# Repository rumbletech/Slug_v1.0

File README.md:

# Slug_v1.0
Slug ( Slog/Serial Logger ) is an open source firmware and an open source hardware project , it implements logging of serial buses like USART,I2C,SPI to an SD Card.

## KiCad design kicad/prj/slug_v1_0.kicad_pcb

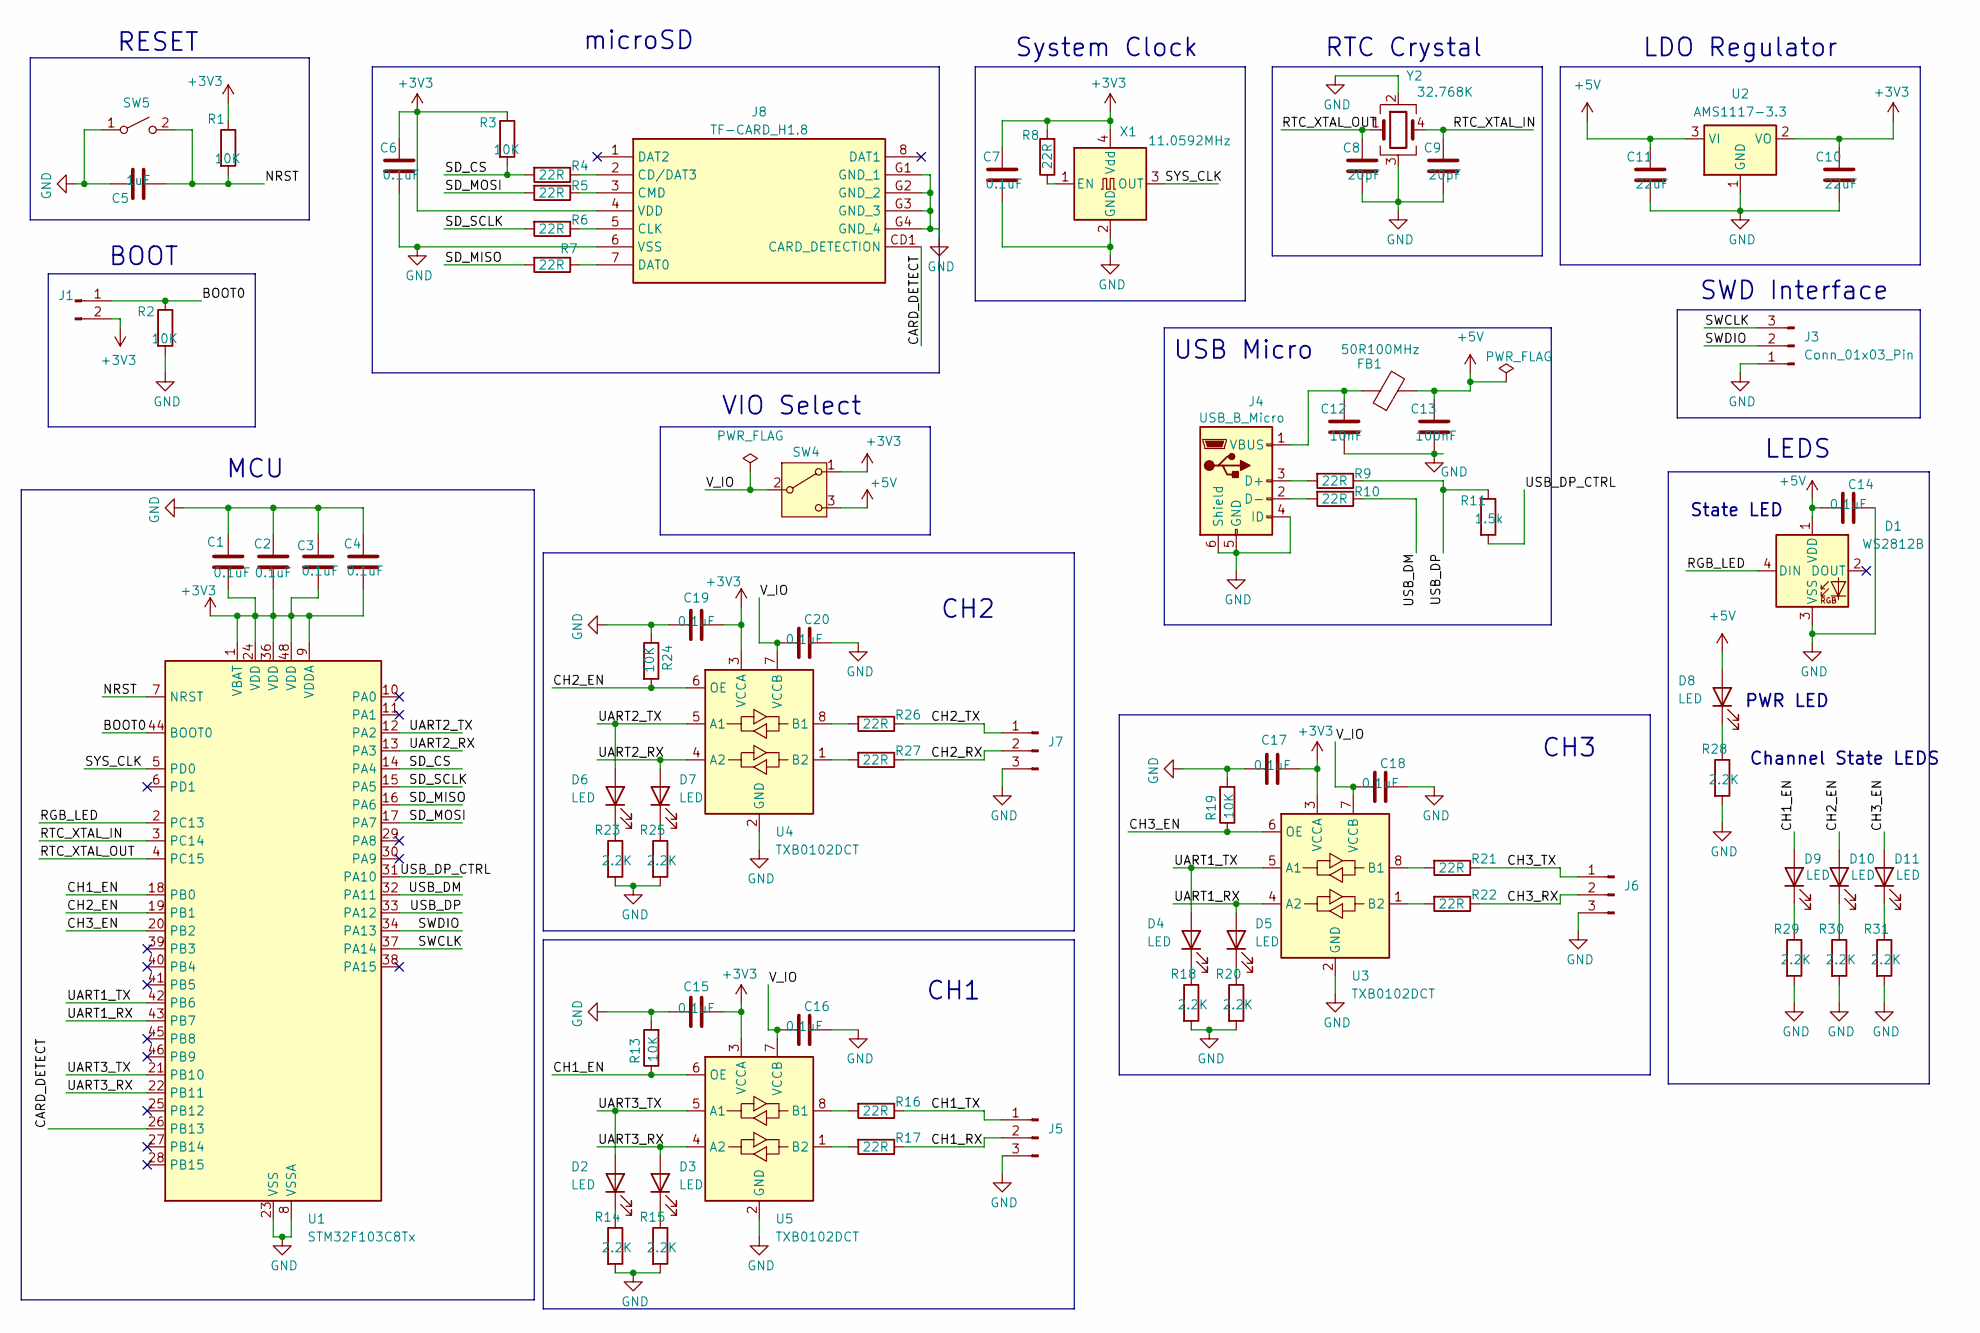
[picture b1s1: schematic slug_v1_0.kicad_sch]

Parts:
C1, C2, C3, C4, C6, C7, C14, C15, C16, C17, C18, C19, C20: 0.1uF; C_0805_2012Metric
C5: 1uF; C_0805_2012Metric
C8, C9: 20pF; C_0805_2012Metric
C10, C11: 22uF; C_0805_2012Metric
C12: 10nF; C_0805_2012Metric
C13: 100nF; C_0805_2012Metric
D1: WS2812B; LED_WS2812B_PLCC4_5.0x5.0mm_P3.2mm
D2, D3, D4, D5, D6, D7, D8, D9, D10, D11: LED; LED_0805_2012Metric
FB1: 50R100MHz; L_0805_2012Metric
J1: Conn_01x02_Pin; PinHeader_1x02_P2.54mm_Vertical
J3: Conn_01x03_Pin; PinHeader_1x03_P2.54mm_Vertical
J4: USB_B_Micro; USB_Micro-B_Amphenol_10118193-0001LF_Horizontal
J5, J6, J7: Conn_01x03_Pin; PinHeader_1x03_P2.54mm_Horizontal
J8: TF-CARD_H1.8; TFCARDH18; Manufacturer_Part_Number TF-CARD H1.8
R1, R2, R3, R13, R19, R24: 10K; R_0805_2012Metric
R4, R5, R6, R7, R8, R9, R10, R16, R17, R21, R22, R26, R27: 22R; R_0805_2012Metric
R11: 1.5k; R_0805_2012Metric
R14, R15, R18, R20, R23, R25, R28, R29, R30, R31: 2.2K; R_0805_2012Metric
SW4: SW_SPDT; SW_SPDT_CK_JS102011SAQN
SW5: SW_SPST; SW_SPST_SKQG_WithStem
U1: STM32F103C8Tx; LQFP-48_7x7mm_P0.5mm
U2: AMS1117-3.3; SOT-223-3_TabPin2
U3, U4, U5: TXB0102DCT; TSSOP-8_3x3mm_P0.65mm
X1: 11.0592MHz; Crystal_SMD_7050-4Pin_7.0x5.0mm
Y2: 32.768K; Crystal_SMD_SeikoEpson_MC306-4Pin_8.0x3.2mm

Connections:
+3V3: C1.2, C2.2, C3.2, C4.2, C6.1, C7.1, C10.1, C15.2, C17.2, C19.2, J1.2, J8.4 (VDD), R1.1, R3.1, R8.2, SW4.1 (A), U1.1 (VBAT), U1.9 (VDDA), U1.24 (VDD), U1.36 (VDD), U1.48 (VDD), U2.2 (VO), U3.3 (VCCA), U4.3 (VCCA), U5.3 (VCCA), X1.4 (Vdd)
+5V: C11.1, C13.1, C14.1, D1.1 (VDD), D8.2 (A), FB1.2, SW4.3 (C), U2.3 (VI)
/BOOT0: J1.1, R2.1, U1.44 (BOOT0)
/CARD_DETECT: J8.CD1 (CARD_DETECTION), U1.26 (PB13)
/CH1_EN: D9.2 (A), R13.1, U1.18 (PB0), U5.6 (OE)
/CH1_RX: J5.2, R17.1
/CH1_TX: J5.1, R16.1
/CH2_EN: D10.2 (A), R24.2, U1.19 (PB1), U4.6 (OE)
/CH2_RX: J7.2, R27.1
/CH2_TX: J7.1, R26.1
/CH3_EN: D11.2 (A), R19.1, U1.20 (PB2), U3.6 (OE)
/CH3_RX: J6.2, R22.1
/CH3_TX: J6.1, R21.1
/NRST: C5.2, R1.2, SW5.2 (B), U1.7 (NRST)
/RGB_LED: D1.4 (DIN), U1.2 (PC13)
/RTC_XTAL_IN: C9.1, U1.3 (PC14), Y2.4
/RTC_XTAL_OUT: C8.1, U1.4 (PC15), Y2.1
/SD_CS: R3.2, R4.2, U1.14 (PA4)
/SD_MISO: R7.2, U1.16 (PA6)
/SD_MOSI: R5.2, U1.17 (PA7)
/SD_SCLK: R6.2, U1.15 (PA5)
/SWCLK: J3.3, U1.37 (PA14)
/SWDIO: J3.2, U1.34 (PA13)
/SYS_CLK: U1.5 (PD0), X1.3 (OUT)
/UART1_RX: D5.2 (A), U1.43 (PB7), U3.4 (A2)
/UART1_TX: D4.2 (A), U1.42 (PB6), U3.5 (A1)
/UART2_RX: D7.2 (A), U1.13 (PA3), U4.4 (A2)
/UART2_TX: D6.2 (A), U1.12 (PA2), U4.5 (A1)
/UART3_RX: D3.2 (A), U1.22 (PB11), U5.4 (A2)
/UART3_TX: D2.2 (A), U1.21 (PB10), U5.5 (A1)
/USB_DM: R10.1, U1.32 (PA11)
/USB_DP: R9.1, R11.1, U1.33 (PA12)
/USB_DP_CTRL: R11.2, U1.31 (PA10)
/V_IO: C16.1, C18.1, C20.1, SW4.2 (B), U3.7 (VCCB), U4.7 (VCCB), U5.7 (VCCB)
GND: C1.1, C2.1, C3.1, C4.1, C5.1, C6.2, C7.2, C8.2, C9.2, C10.2, C11.2, C12.2, C13.2, C14.2, C15.1, C16.2, C17.1, C18.2, C19.1, C20.2, D1.3 (VSS), J3.1, J4.4 (ID), J4.5 (GND), J4.6 (Shield), J5.3, J6.3, J7.3, J8.6 (VSS), J8.G1 (GND_1), J8.G2 (GND_2), J8.G3 (GND_3), J8.G4 (GND_4), R2.2, R13.2, R14.2, R15.2, R18.2, R19.2, R20.2, R23.2, R24.1, R25.2, R28.2, R29.2, R30.2, R31.2, SW5.1 (A), U1.8 (VSSA), U1.23 (VSS), U1.35 (VSS), U1.47 (VSS), U2.1 (GND), U3.2 (GND), U4.2 (GND), U5.2 (GND), X1.2 (GND), Y2.2, Y2.3
unnamed: D2.1 (K), R14.1
unnamed: D3.1 (K), R15.1
unnamed: D4.1 (K), R18.1
unnamed: D5.1 (K), R20.1
unnamed: D6.1 (K), R23.1
unnamed: D7.1 (K), R25.1
unnamed: D8.1 (K), R28.1
unnamed: D9.1 (K), R29.1
unnamed: D10.1 (K), R30.1
unnamed: D11.1 (K), R31.1
unnamed: J4.3 (D+), R9.2
unnamed: J4.2 (D-), R10.2
unnamed: C12.1, FB1.1, J4.1 (VBUS)
unnamed: J8.2 (CD/DAT3), R4.1
unnamed: J8.5 (CLK), R6.1
unnamed: J8.3 (CMD), R5.1
unnamed: J8.7 (DAT0), R7.1
unnamed: R21.2, U3.8 (B1)
unnamed: R22.2, U3.1 (B2)
unnamed: R26.2, U4.8 (B1)
unnamed: R27.2, U4.1 (B2)
unnamed: R16.2, U5.8 (B1)
unnamed: R17.2, U5.1 (B2)
unnamed: R8.1, X1.1 (EN)

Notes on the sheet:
State LED
MCU
CH1
RTC Crystal
CH2
System Clock
microSD
CH3
LDO Regulator
RESET
USB Micro
Channel State LEDS
BOOT
VIO Select
PWR LED
SWD Interface
LEDS

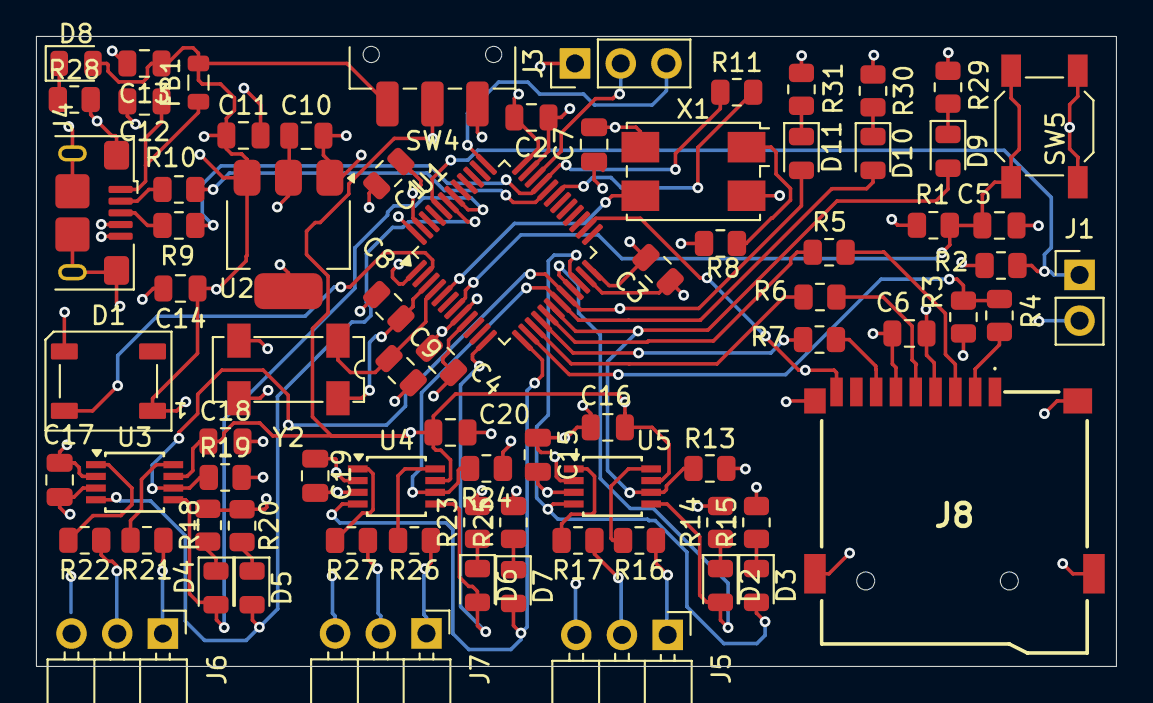
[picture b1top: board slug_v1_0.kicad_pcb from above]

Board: 4 copper layers, 60.0 x 35.0 mm, 78 parts (0 on the bottom side), 59 nets.

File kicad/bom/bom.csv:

Designator,Footprint,Quantity,Value,LCSC Part #
"C1, C13, C15, C16, C17, C18, C19, C2, C20, C3, C4, C6, C7",805,13,0.1uF,C28233 
"C10, C11",805,2,10uF,C15850 
C12,805,1,10nF,C1710 
C5,805,1,1uF,C28323
"C8, C9",805,2,20pF,C1798
"D2, D4, D6",805,3,LED,C2296
"D3, D5, D7, D8",805,4,LED,C2297
"D10, D11, D9",805,3,LED,C2297
D12,SMD5050-6Pin,1,LED_RGB,C111658 
FB1,805,1,50R100MHz,C1015 
IC1,TSOT-23-5,1,RT9080-33GJ5,C841192 
J4,USB_Micro-B_MOLEX_105017,1,USB_B_Micro,C505111 
J8,TFCARDH18,1,TF-CARD_H1.8,C7529389 
"R1, R13, R19, R2, R24, R3",805,6,10K,C17414
"R10, R16, R17, R21, R22, R26, R27, R4, R5, R6, R7, R8, R9",805,13,22R,C17561
R11,805,1,1.5k,C4310
"R12, R32, R33",805,3,1k,C17513
"R14, R15, R18, R20, R23, R25, R28, R29, R30, R31",805,10,2.2K,C17520
SW5,SW_SPST_SKQG_WithStem,1,SW_SPST,C202424 
U1,LQFP-48_7x7mm_P0.5mm,1,STM32F103C8Tx,C8304 
"U3, U4, U5",VSSOP-8_2.3x2mm_P0.5mm,3,TXB0102DCT,C2677366 
X1,Crystal_SMD_7050-4Pin_7.0x5.0mm,1,8MHz,C242205 
Y2,Crystal_SMD_MC306-4Pin_8.0x3.2mm,1,32.768K,C12675

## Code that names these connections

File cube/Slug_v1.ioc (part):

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Mcu.Name=STM32F103C(8-B)Tx
Mcu.Package=LQFP48
Mcu.UserName=STM32F103CBTx
PA10.Signal=GPIO_Output
PA11.Mode=Device
PA11.Signal=USB_DM
PA12.Mode=Device
PA12.Signal=USB_DP
PA13.Mode=Serial_Wire
PA13.Signal=SYS_JTMS-SWDIO
PA14.Mode=Serial_Wire
PA14.Signal=SYS_JTCK-SWCLK
PA2.Mode=Asynchronous
PA2.Signal=USART2_TX
PA3.Mode=Asynchronous
PA3.Signal=USART2_RX
PA4.Mode=NSS_Signal_Hard_Output
PA4.Signal=SPI1_NSS
PA5.Mode=Full_Duplex_Master
PA5.Signal=SPI1_SCK
PA6.Mode=Full_Duplex_Master
PA6.Signal=SPI1_MISO
PA7.Mode=Full_Duplex_Master
PA7.Signal=SPI1_MOSI
PB0.Signal=GPIO_Output
PB1.Signal=GPIO_Output
PB10.Mode=Asynchronous
PB10.Signal=USART3_TX
PB11.Mode=Asynchronous
PB11.Signal=USART3_RX
PB2.Signal=GPIO_Output
PB3.Signal=GPIO_Output
PB4.Signal=GPIO_Output
PB5.Signal=GPIO_Output
PB6.Mode=Asynchronous
PB6.Signal=USART1_TX
PB7.Mode=Asynchronous
PB7.Signal=USART1_RX
PC14-OSC32_IN.Mode=LSE-External-Clock-Source
PC14-OSC32_IN.Signal=RCC_OSC32_IN
PC15-OSC32_OUT.Mode=LSE-External-Clock-Source
PC15-OSC32_OUT.Signal=RCC_OSC32_OUT
PD0-OSC_IN.Mode=HSE-External-Clock-Source
PD0-OSC_IN.Signal=RCC_OSC_IN
PD1-OSC_OUT.Mode=HSE-External-Clock-Source
PD1-OSC_OUT.Signal=RCC_OSC_OUT
RCC.SYSCLKFreq_VALUE=72000000
RCC.SYSCLKSource=RCC_SYSCLKSOURCE_PLLCLK
board=custom

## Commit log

2024-09-28 Add Initial eclipse project , and added example .json configuration file.
2024-10-05 Added Debug , Project Options , and USART1 to HAL/IOC.
2024-10-05 Fix HSE Freq to 8MHz , Add Printf Example.
2024-10-05 Update Hal_conf after Frequency change , update .gitignore.
2024-10-06 Add SPI1 to IOC/Hal.
2024-10-06 Add Fatfs lib , GPIO handle , SPI1 and SDC driver.
2024-10-18 SD Card patch 1.
2024-10-19 SD Card patch 2.
2024-10-26 SD Card Patch 3.
2024-10-26 SD Card Patch 4.
2024-10-26 SD Card Patch 5.
2025-04-20 Add RGB module and fix compilation errors.
2025-04-25 Added Kicad project files , bom and gerbers and major fw update.
    - Added USB Device lib.
    - changes part to STM32F103CBT6 (128kb flash).
    - Added drivers for rgb led and channel enable pins.
    - Added JSMN jason parser.
    - Added working small app to read json configuration and configure
    channels.
2025-05-05 Working UART IRQ
    TBD:
    - Move to light weight SPI driver.
    - Move to light weight UART driver.
    - Move to light weight GPIO driver.
    - Move to tinyusb + freeRTOS instead of HAL.
2025-05-12 Removed USB Device.
2025-05-12 - Updates.
    - Added lwDriver instead of HAL.
    - Added GPIO/SPI/RCC Drivers.
    - Added BSP and self contained modules.
    - Remove redundant module SDC_SPI.c
    - TBD : SPI PIN AF Add to lw_gpio.
    - TBD : Make clock configuration in lw_rcc
2025-05-18 - Removed Dependency on HAL_SPI and HAL_GPIO on SDCD Module.
    - Fixed BSP MOSI pin number.
    - Added GPIO Mode and CFG to lwGPIO.
2025-05-30 Remove HAL_UART dependency and add lw_UART driver.
2025-06-08 Add Clock Init functions , remove HAL , extra CMSIS Files removed.
2025-06-13 Rework Com_Channel module , add final lwDrivers , add clock init.
    remove file_sys module and move logic to application.
2025-06-14 Added FreeRTOS to the project.
2025-06-14 Remove un-needed files from freeRTOS
2025-06-14 Add TickHook to RTOS , remove driver to driver dependencies and move init to system init function.
2025-06-26 Add FSM and DISK thread handlers.
2025-06-28 First Working SDC Variant
    - Added Automatic writing and flushing io operations.
    - Replaced fifo with ping pong buffers.
    - Write Cyclicity to 100 ms
    - Flush Cyclicity to 1s.
2025-07-13 Add Working Card Detection.
